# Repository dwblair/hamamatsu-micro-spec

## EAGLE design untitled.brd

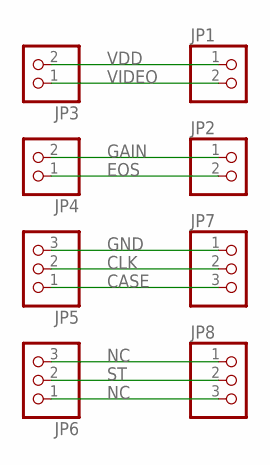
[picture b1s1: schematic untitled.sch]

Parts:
JP1, JP2, JP3, JP4: PINHD-1X2; 1X02
JP5, JP6, JP7, JP8: PINHD-1X3; 1X03

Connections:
CASE: JP5.1, JP7.3
CLK: JP5.2, JP7.2
EOS: JP2.2, JP4.1
GAIN: JP2.1, JP4.2
GND: JP5.3, JP7.1
NC: JP6.1, JP6.3, JP8.1, JP8.3
ST: JP6.2, JP8.2
VDD: JP1.1, JP3.2
VIDEO: JP1.2, JP3.1

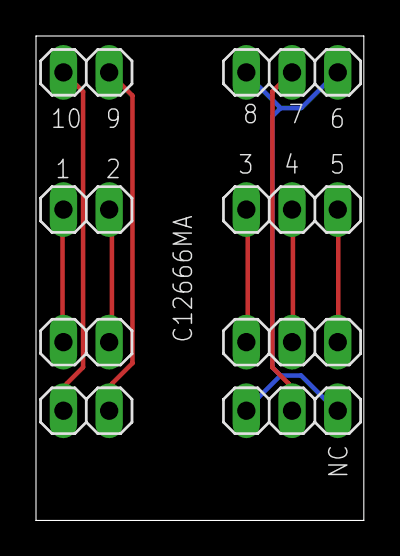
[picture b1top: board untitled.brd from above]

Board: 2 copper layers, 18.2 x 26.9 mm, 8 parts (0 on the bottom side), 9 nets.
